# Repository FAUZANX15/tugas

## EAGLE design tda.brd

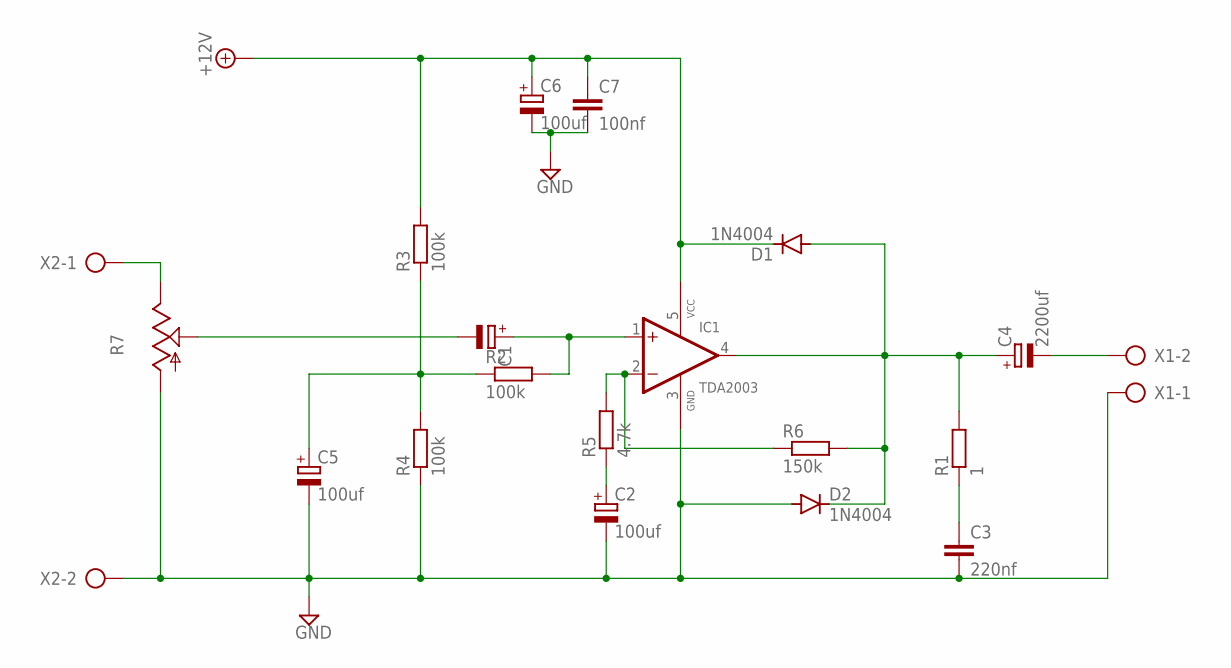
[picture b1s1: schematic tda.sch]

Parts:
C1: CPOL-EUE2-5; E2-5
C2, C5, C6: 100uf; E2-5
C3: 220nf; C025-030X050
C4: 2200uf; E2-5
C7: 100nf; C025-030X050
D1, D2: 1N4004; DO41-10
IC1: TDA2003; PENTAWATT-V
R1: 1; 0309/12
R2, R3, R4: 100k; 0309/12
R5: 4.7k; 0309/12
R6: 150k; 0309/12
R7: TRIM_US-CIP20C-6MM; CIP20C-6MM
X1, X2: AK300/2

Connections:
+12V: C6.+, C7.1, D1.C, IC1.5 (VCC), R3.2
GND: C2.-, C3.2, C5.-, C6.-, C7.2, D2.A, IC1.3 (GND), R4.1, R7.A, X1.1, X2.2
unnamed: C4.-, X1.2
unnamed: C4.+, D1.A, D2.C, IC1.4 (OUT), R1.2, R6.2
unnamed: C3.1, R1.1
unnamed: C1.-, R7.S
unnamed: R7.E, X2.1
unnamed: IC1.2 (-IN), R5.2, R6.1
unnamed: C2.+, R5.1
unnamed: C1.+, IC1.1 (+IN), R2.2
unnamed: C5.+, R2.1, R3.1, R4.2

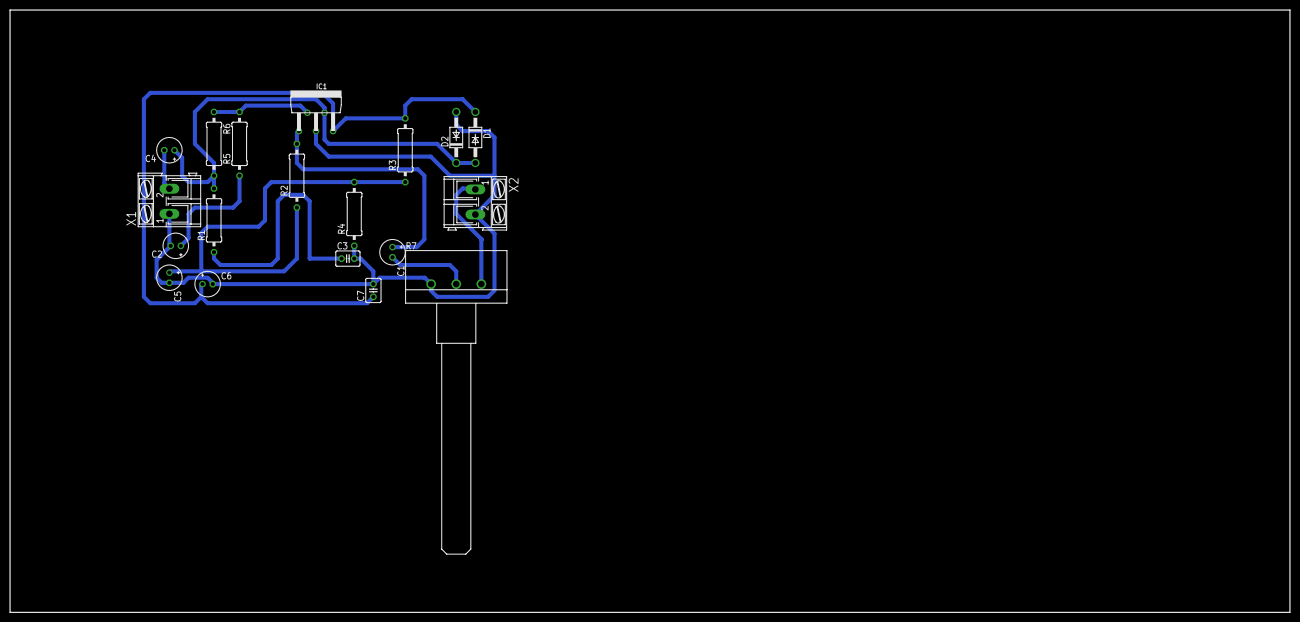
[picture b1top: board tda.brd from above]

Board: 2 copper layers, 255.0 x 120.0 mm, 19 parts (0 on the bottom side), 11 nets.
